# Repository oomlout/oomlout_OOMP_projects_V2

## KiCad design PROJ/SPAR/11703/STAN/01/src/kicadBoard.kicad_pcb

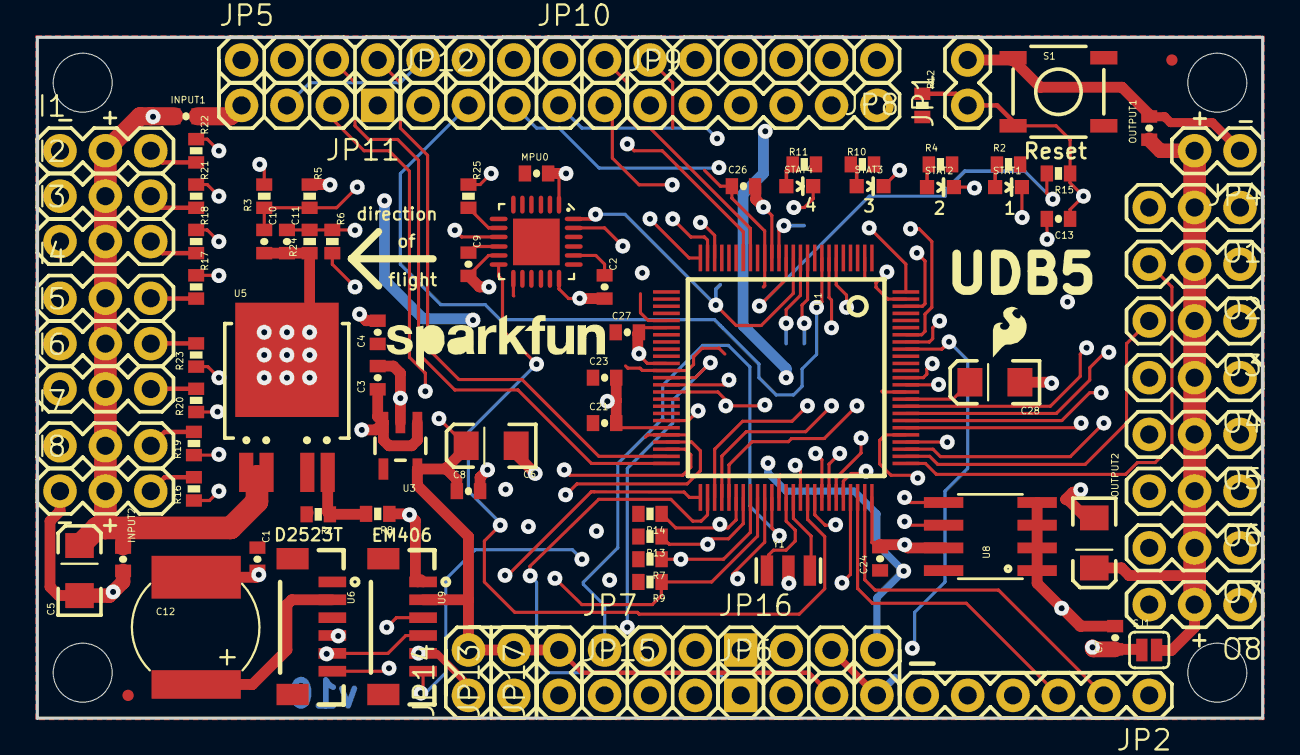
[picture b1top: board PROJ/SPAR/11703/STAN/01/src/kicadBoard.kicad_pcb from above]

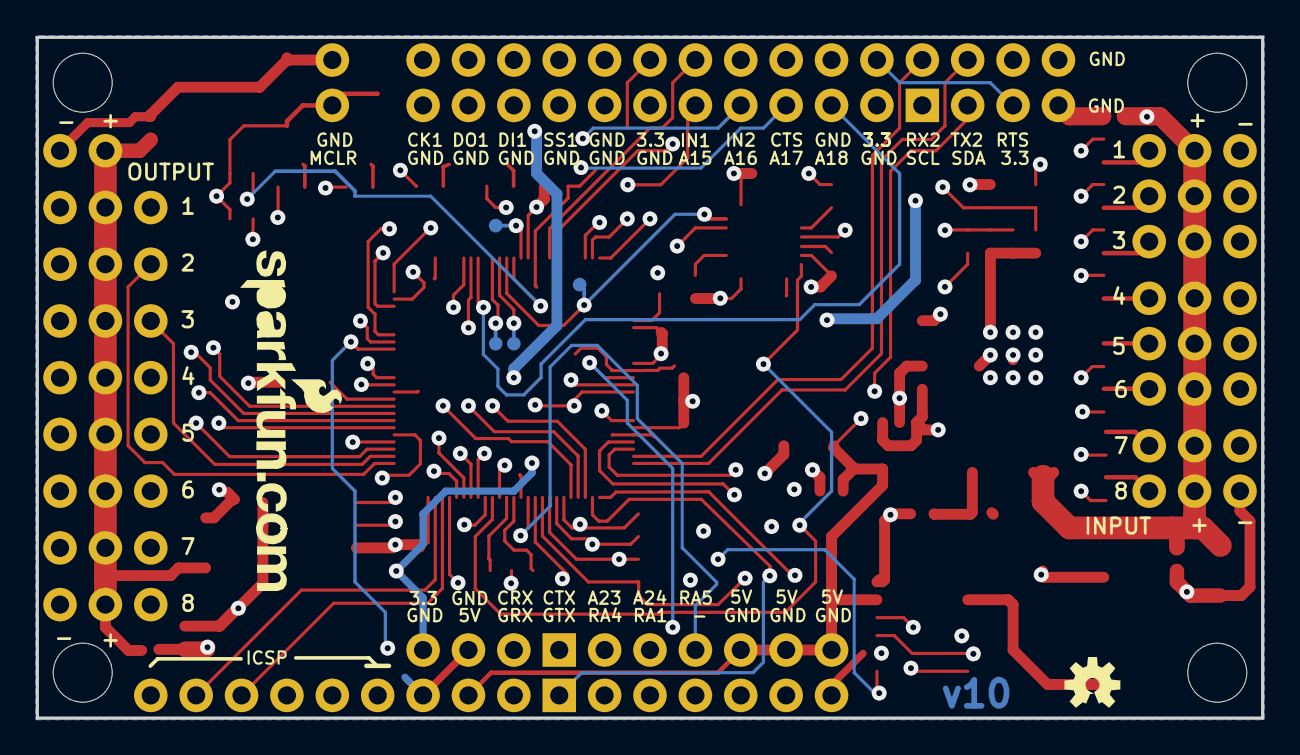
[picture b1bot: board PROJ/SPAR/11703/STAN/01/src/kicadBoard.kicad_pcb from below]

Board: 4 copper layers, 68.6 x 38.1 mm, 110 parts (6 on the bottom side), 84 nets.

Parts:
C1, C3: 1uF; 0402-CAP
C2: 2.2nF; 0402-CAP
C4, C7, C8, C9, C13, C21, C23, C24, C26, C27: 0.1uF; 0402-CAP
C5, C6, C28: 10uF; EIA3216
C10, C11: 22nF; 0402-CAP
C12: 0.2F/3.3V; EN_J2
CC_TEXT1: CREATIVE_COMMONS
I1, I2, I3, I4, I5, I6, I7, I8: S; 1X03
INPUT1, INPUT2: 0.1uF; 0402-CAP
JP1: EXT_Reset; 1X02
JP2: prog; 1X06
JP3: LOGO-SFENEW; SFE-NEW-WEBLOGO
JP4: SVCC; 1X02
JP5: ST; 1X07
JP6: SG; 1X04
JP7, JP15: extra; 1X03
JP8: SPI1; 1X06
JP9: GND; 1X06
JP10: INT; 1X02
JP11: I2C; 1X04
JP12: ACOM1; 1X05
JP13, JP14, JP17: power; 1X02
JP16: extra; 1X04
JP18, JP19: FIDUCIAL1X2.5; FIDUCIAL-1X2.5
LOGO1: LOGO-SFENW2; SFE-NEW-WEB
MPU0: 0.1uF; 0402-CAP
O1, O2, O3, O4, O5, O6, O7, O8: RA; 1X03
OUTPUT1: 0.1uF; 0402-CAP
OUTPUT2: 10uF; EIA3216
R1: 20k; 0402-RES
R2, R4, R10, R11, R16, R17, R18, R19, R20, R21, R22, R23: 330; 0402-RES
R3, R5, R6, R12, R24: 10k; 0402-RES
R7, R9, R13, R14: 4.7k; 0402-RES
R8: 12.1k; 0402-RES
R15: 470; 0402-RES
R25: 1k; 0402-RES
S1: SWITCH-MOMENTARY-2SMD; TACTILE_SWITCH_SMD
SJ1: SOLDERJUMPERNC; SJ_2S
STAT1: red; LED-0603
STAT2: green; LED-0603
STAT3: yellow; LED-0603
STAT4: blue; LED-0603
TP1, TP2, TP3, TP4: TEST-POINT3; PAD.03X.03
U1: DSPIC33FJ256GP710_; TQFP-100-12X12MM
U3: V_REG_LDOSMD; SOT23-5
U5: V_REG_NCP50X; DPAK-5
U6: D2523T_; EM406
U8: EEPROM-I2CSMD; SO08
U9: EM406
U10: MPU-6000QFN-24; QFN-24-TESTING
U$2, U$3, U$4, U$5: STAND-OFF
U$9: OSHW-LOGOS; OSHW-LOGO-S
U$10: LOGO-SFESK; SFE-LOGO-FLAME
Y1: RESONATORSMD; RESONATOR-SMD

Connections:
3.3V: C1.1, C4.1, C21.1, C23.1, C24.1, C26.1, C27.1, JP2.5, JP5.5, JP8.6, JP11.3, JP16.4, MPU0.1, R1.2, R2.2, R4.2, R7.2, R9.2, R10.2, R11.2, R12.2, R13.2, R14.2, U1.2, U1.16, U1.30, U1.37, U1.46, U1.62, U1.86, U5.VOUT, U6.3, U8.8, U10.13
5V: C6.A, C8.1, JP6.3, JP13.2, JP14.2, JP17.2, R6.2, U3.5, U9.2
A-5V: C11.1, R6.1, R24.2, U1.24
A-VCC: C10.1, R3.1, R5.2, U1.25
AN15: JP12.5, U1.44
AN16: JP12.4, U1.6
AN17: JP12.3, U1.7
AN18: JP12.2, U1.8
AN23: JP7.3, U1.92
AN24: JP7.2, U1.93
CRX: JP16.2, U1.87
CTS2: JP5.7, U1.40
CTX: JP16.1, U1.88
GND: C1.2, C2.2, C3.2, C4.2, C5.C, C6.C, C7.2, C8.2, C9.2, C10.2, C11.2, C12.-, C13.2, C21.2, C23.2, C24.2, C26.2, C27.2, C28.C, I1.1, I2.1, I3.1, I4.1, I5.1, I6.1, I7.1, I8.1, INPUT1.2, INPUT2.2, JP1.2, JP2.4, JP4.1, JP5.1, JP5.6, JP6.4, JP8.5, JP9.1, JP9.2, JP9.3, JP9.4, JP9.5, JP9.6, JP11.4, JP12.1, JP13.1, JP14.1, JP16.3, JP17.1, MPU0.2, O1.1, O2.1, O3.1, O4.1, O5.1, O6.1, O7.1, O8.1, OUTPUT1.2, OUTPUT2.C, R5.1, R8.1, R24.1, S1.1, U1.15, U1.31, U1.36, U1.45, U1.65, U1.75, U3.2, U5.GND, U6.4, U8.1, U8.2, U8.3, U8.4, U8.7, U9.1, U9.5, U10.1, U10.11, U10.18, Y1.2
GPS_PPS: U1.67, U9.6
GPS_RX: JP6.2, U1.51, U6.6, U9.3
GPS_TX: JP6.1, U1.52, U6.5, U9.4
I1: R22.1, U1.68
I2: R21.1, U1.69
I3: R18.1, U1.70
I4: R17.1, U1.71
I5: R23.1, U1.79
I6: R20.1, U1.80
I7: R19.1, U1.47
I8: R16.1, U1.48
INT1: JP10.2, U1.18
INT2: JP10.1, U1.19
LED1: STAT1.C, U1.94
LED2: STAT2.C, U1.98
LED3: STAT3.C, U1.99
LED4: STAT4.C, U1.100
MCLR: C13.1, JP1.1, JP2.6, R12.1, R15.1, S1.3
MPU-CS: R25.1, TP1.P$1, U1.14
MPU-INT: U1.66, U10.12
MPU-MISO: TP3.P$1, U1.11, U10.9
MPU-MOSI: TP4.P$1, U1.12, U10.24
MPU-SCK: TP2.P$1, U1.10, U10.23
unnamed: R2.1, STAT1.A
unnamed: R4.1, STAT2.A
unnamed: U1.64, Y1.3
unnamed: C12.+, U6.2
unnamed: R25.2, U10.8
unnamed: U1.63, Y1.1
unnamed: R15.2, U1.13
unnamed: R1.1, R8.2, U5.ADJ
unnamed: C2.1, U10.20
unnamed: I8.3, R16.2
unnamed: I4.3, R17.2
unnamed: C9.1, U10.10
unnamed: I3.3, R18.2
unnamed: I7.3, R19.2
unnamed: I6.3, R20.2
unnamed: I2.3, R21.2
unnamed: I1.3, R22.2
unnamed: I5.3, R23.2
unnamed: R10.1, STAT3.A
unnamed: R11.1, STAT4.A
unnamed: C28.A, U1.85
O1: O1.3, U1.72
O2: O2.3, U1.76
O3: O3.3, U1.77
O4: O4.3, U1.78
O5: O5.3, U1.81
O6: O6.3, U1.82
O7: O7.3, U1.83
O8: O8.3, U1.84
PGEC2: JP2.2, U1.74
PGED2: JP2.3, U1.73
RA1: JP15.2, U1.38
RA4: JP15.3, U1.60
RA5: JP7.1, U1.61
RTS2: JP5.2, U1.39
RX2: JP5.4, U1.49
SCK1: JP8.1, U1.55
SCL1: R13.1, U1.57, U8.6
SCL2: JP11.1, R7.1, U1.58
SDA1: R14.1, U1.56, U8.5
SDA2: JP11.2, R9.1, U1.59
SDI1: JP8.3, U1.54
SDO1: JP8.2, U1.53
SS1: JP8.4, U1.23
SVCC: JP4.2, O1.2, O2.2, O3.2, O4.2, O5.2, O6.2, O7.2, O8.2, OUTPUT1.1, OUTPUT2.A, SJ1.2
TX2: JP5.3, U1.50
VCC: C3.1, C5.A, C7.1, I1.2, I2.2, I3.2, I4.2, I5.2, I6.2, I7.2, I8.2, INPUT1.1, INPUT2.1, R3.2, SJ1.1, U3.1, U3.3, U5.EN, U5.VIN

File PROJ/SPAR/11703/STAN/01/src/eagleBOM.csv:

"Part";"Value";"Device";"Package";"Description";"";
"C1";"1uF";"CAP0402-CAP";"0402-CAP";"Capacitor";"";
"C2";"2.2nF";"CAP0402-CAP";"0402-CAP";"Capacitor";"";
"C3";"1uF";"CAP0402-CAP";"0402-CAP";"Capacitor";"";
"C4";"0.1uF";"CAP0402-CAP";"0402-CAP";"Capacitor";"";
"C5";"10uF";"CAP_POL1206";"EIA3216";"Capacitor Polarized";"";
"C6";"10uF";"CAP_POL1206";"EIA3216";"Capacitor Polarized";"";
"C7";"0.1uF";"CAP0402-CAP";"0402-CAP";"Capacitor";"";
"C8";"0.1uF";"CAP0402-CAP";"0402-CAP";"Capacitor";"";
"C9";"0.1uF";"CAP0402-CAP";"0402-CAP";"Capacitor";"";
"C10";"22nF";"CAP0402-CAP";"0402-CAP";"Capacitor";"";
"C11";"22nF";"CAP0402-CAP";"0402-CAP";"Capacitor";"";
"C12";"0.2F/3.3V";"CAP_POLEN_J2";"EN_J2";"Capacitor Polarized";"";
"C13";"0.1uF";"CAP0402-CAP";"0402-CAP";"Capacitor";"";
"C21";"0.1uF";"CAP0402-CAP";"0402-CAP";"Capacitor";"";
"C23";"0.1uF";"CAP0402-CAP";"0402-CAP";"Capacitor";"";
"C24";"0.1uF";"CAP0402-CAP";"0402-CAP";"Capacitor";"";
"C26";"0.1uF";"CAP0402-CAP";"0402-CAP";"Capacitor";"";
"C27";"0.1uF";"CAP0402-CAP";"0402-CAP";"Capacitor";"";
"C28";"10uF";"CAP_POL1206";"EIA3216";"Capacitor Polarized";"";
"CC_TEXT1";"CREATIVE_COMMONS";"CREATIVE_COMMONS";"CREATIVE_COMMONS";"Creative Commons License summary";"";
"I1";"S";"M03PTH";"1X03";"Header 3";"";
"I2";"S";"M03PTH";"1X03";"Header 3";"";
"I3";"S";"M03PTH";"1X03";"Header 3";"";
"I4";"S";"M03PTH";"1X03";"Header 3";"";
"I5";"S";"M03PTH";"1X03";"Header 3";"";
"I6";"S";"M03PTH";"1X03";"Header 3";"";
"I7";"S";"M03PTH";"1X03";"Header 3";"";
"I8";"S";"M03PTH";"1X03";"Header 3";"";
"INPUT1";"0.1uF";"CAP0402-CAP";"0402-CAP";"Capacitor";"";
"INPUT2";"0.1uF";"CAP0402-CAP";"0402-CAP";"Capacitor";"";
"JP1";"EXT_Reset";"M02PTH";"1X02";"Header 2";"";
"JP2";"prog";"M06SIP";"1X06";"Header 6";"";
"JP3";"LOGO-SFENEW";"LOGO-SFENEW";"SFE-NEW-WEBLOGO";"Spark Fun Electronics PCB Logo";"";
"JP4";"SVCC";"M02PTH";"1X02";"Header 2";"";
"JP5";"ST";"M07";"1X07";"Header 7";"";
"JP6";"SG";"M04PTH";"1X04";"Header 4";"";
"JP7";"extra";"M03PTH";"1X03";"Header 3";"";
"JP8";"SPI1";"M06SIP";"1X06";"Header 6";"";
"JP9";"GND";"M06SIP";"1X06";"Header 6";"";
"JP10";"INT";"M02PTH";"1X02";"Header 2";"";
"JP11";"I2C";"M04PTH";"1X04";"Header 4";"";
"JP12";"ACOM1";"M05PTH";"1X05";"Header 5";"";
"JP13";"power";"M02PTH";"1X02";"Header 2";"";
"JP14";"power";"M02PTH";"1X02";"Header 2";"";
"JP15";"extra";"M03PTH";"1X03";"Header 3";"";
"JP16";"extra";"M04PTH";"1X04";"Header 4";"";
"JP17";"power";"M02PTH";"1X02";"Header 2";"";
"JP18";"FIDUCIAL1X2.5";"FIDUCIAL1X2.5";"FIDUCIAL-1X2.5";"Fiducial Alignment Points";"";
"JP19";"FIDUCIAL1X2.5";"FIDUCIAL1X2.5";"FIDUCIAL-1X2.5";"Fiducial Alignment Points";"";
"LOGO1";"LOGO-SFENW2";"LOGO-SFENW2";"SFE-NEW-WEB";"Spark Fun Electronics PCB Logo";"";
"MPU";"0.1uF";"CAP0402-CAP";"0402-CAP";"Capacitor";"";
"O1";"RA";"M03PTH";"1X03";"Header 3";"";
"O2";"RA";"M03PTH";"1X03";"Header 3";"";
"O3";"RA";"M03PTH";"1X03";"Header 3";"";
"O4";"RA";"M03PTH";"1X03";"Header 3";"";
"O5";"RA";"M03PTH";"1X03";"Header 3";"";
"O6";"RA";"M03PTH";"1X03";"Header 3";"";
"O7";"RA";"M03PTH";"1X03";"Header 3";"";
"O8";"RA";"M03PTH";"1X03";"Header 3";"";
"OUTPUT1";"0.1uF";"CAP0402-CAP";"0402-CAP";"Capacitor";"";
"OUTPUT2";"10uF";"CAP_POL1206";"EIA3216";"Capacitor Polarized";"";
"R1";"20k";"RESISTOR0402-RES";"0402-RES";"Resistor";"";
"R2";"330";"RESISTOR0402-RES";"0402-RES";"Resistor";"";
"R3";"10k";"RESISTOR0402-RES";"0402-RES";"Resistor";"";
"R4";"330";"RESISTOR0402-RES";"0402-RES";"Resistor";"";
"R5";"10k";"RESISTOR0402-RES";"0402-RES";"Resistor";"";
"R6";"10k";"RESISTOR0402-RES";"0402-RES";"Resistor";"";
"R7";"4.7k";"RESISTOR0402-RES";"0402-RES";"Resistor";"";
"R8";"12.1k";"RESISTOR0402-RES";"0402-RES";"Resistor";"";
"R9";"4.7k";"RESISTOR0402-RES";"0402-RES";"Resistor";"";
"R10";"330";"RESISTOR0402-RES";"0402-RES";"Resistor";"";
"R11";"330";"RESISTOR0402-RES";"0402-RES";"Resistor";"";
"R12";"10k";"RESISTOR0402-RES";"0402-RES";"Resistor";"";
"R13";"4.7k";"RESISTOR0402-RES";"0402-RES";"Resistor";"";
"R14";"4.7k";"RESISTOR0402-RES";"0402-RES";"Resistor";"";
"R15";"470";"RESISTOR0402-RES";"0402-RES";"Resistor";"";
"R16";"330";"RESISTOR0402-RES";"0402-RES";"Resistor";"";
"R17";"330";"RESISTOR0402-RES";"0402-RES";"Resistor";"";
"R18";"330";"RESISTOR0402-RES";"0402-RES";"Resistor";"";
"R19";"330";"RESISTOR0402-RES";"0402-RES";"Resistor";"";
"R20";"330";"RESISTOR0402-RES";"0402-RES";"Resistor";"";
"R21";"330";"RESISTOR0402-RES";"0402-RES";"Resistor";"";
"R22";"330";"RESISTOR0402-RES";"0402-RES";"Resistor";"";
"R23";"330";"RESISTOR0402-RES";"0402-RES";"Resistor";"";
"R24";"10k";"RESISTOR0402-RES";"0402-RES";"Resistor";"";
"R25";"1k";"RESISTOR0402-RES";"0402-RES";"Resistor";"";
"S1";"SWITCH-MOMENTARY-2SMD";"SWITCH-MOMENTARY-2SMD";"TACTILE_SWITCH_SMD";"";"";
"SJ1";"SOLDERJUMPERNC";"SOLDERJUMPERNC";"SJ_2S";"Solder Jumper";"";
"STAT1";"red";"LED0603";"LED-0603";"LEDs";"";
"STAT2";"green";"LED0603";"LED-0603";"LEDs";"";
"STAT3";"yellow";"LED0603";"LED-0603";"LEDs";"";
"STAT4";"blue";"LED0603";"LED-0603";"LEDs";"";
"TP1";"TEST-POINT3";"TEST-POINT3";"PAD.03X.03";"Bare copper test points for troubleshooting or ICT";"";
"TP2";"TEST-POINT3";"TEST-POINT3";"PAD.03X.03";"Bare copper test points for troubleshooting or ICT";"";
"TP3";"TEST-POINT3";"TEST-POINT3";"PAD.03X.03";"Bare copper test points for troubleshooting or ICT";"";
"TP4";"TEST-POINT3";"TEST-POINT3";"PAD.03X.03";"Bare copper test points for troubleshooting or ICT";"";
"U$2";"STAND-OFF";"STAND-OFF";"STAND-OFF";"Stand Off";"";
"U$3";"STAND-OFF";"STAND-OFF";"STAND-OFF";"Stand Off";"";
"U$4";"STAND-OFF";"STAND-OFF";"STAND-OFF";"Stand Off";"";
"U$5";"STAND-OFF";"STAND-OFF";"STAND-OFF";"Stand Off";"";
"U$9";"OSHW-LOGOS";"OSHW-LOGOS";"OSHW-LOGO-S";"Open Source Hardware Logo This logo indicates the piece of hardware it is found on incorporates a OSHW license and/or adheres to the definition of open source hardware found here: http://freedomdefined.org/OSHW";"";
"U$10";"LOGO-SFESK";"LOGO-SFESK";"SFE-LOGO-FLAME";"Spark Fun Electronics PCB Logo";"";
"U1";"DSPIC33FJ256GP710_";"DSPIC33FJ256GP710_";"TQFP-100-12X12MM";"";"";
"U3";"V_REG_LDOSMD";"V_REG_LDOSMD";"SOT23-5";"Voltage Regulator LDO";"";
"U5";"V_REG_NCP50X";"V_REG_NCP50X";"DPAK-5";"NCP550x 500mA LDO Voltage Regulator";"";
"U6";"D2523T_";"D2523T_";"EM406";"D2523T GPS Module";"";
"U8";"EEPROM-I2CSMD";"EEPROM-I2CSMD";"SO08";"";"";
"U9";"EM406";"EM406";"EM406";"EM406 Connector";"";
"U10";"MPU-6000QFN-24";"MPU-6000QFN-24";"QFN-24-TESTING";"MPU-6000 - I2C address is 0x68 with AD0 low and 0x69 with AD0 high.";"";
"Y1";"RESONATORSMD";"RESONATORSMD";"RESONATOR-SMD";"Resonator";"";

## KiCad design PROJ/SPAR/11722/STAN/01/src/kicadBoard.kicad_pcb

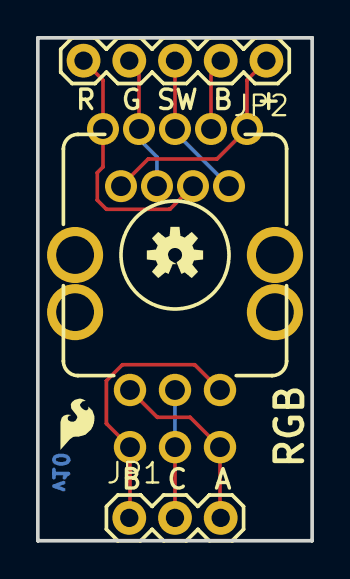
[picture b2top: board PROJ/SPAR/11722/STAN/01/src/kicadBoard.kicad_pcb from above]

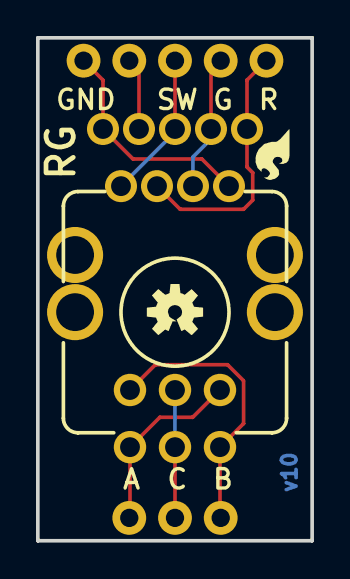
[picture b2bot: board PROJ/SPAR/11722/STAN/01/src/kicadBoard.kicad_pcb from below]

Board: 2 copper layers, 15.2 x 27.9 mm, 9 parts (3 on the bottom side), 8 nets.

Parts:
FRAME1: FRAME-LETTER; CREATIVE_COMMONS
JP1: 1X03
JP2: 1X05
JP3, JP4: LOGO-SFESK; SFE-LOGO-FLAME
SW1: ENCODER_LED_3_KIT
U1: ENCODER_2LEDKIT; ENCODER_LED_2_KIT
U$1, U$2: OSHW-LOGOS; OSHW-LOGO-S

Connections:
A: JP1.3, SW1.A, U1.A
B: JP1.1, SW1.B, U1.B
BLUE: JP2.2, SW1.4
C: JP1.2, SW1.C, U1.C
COMMON: JP2.1, SW1.5, U1.GND
GREEN: JP2.4, SW1.2, U1.+G
RED: JP2.5, SW1.1, U1.+R
SWITCH: JP2.3, SW1.3, U1.SW

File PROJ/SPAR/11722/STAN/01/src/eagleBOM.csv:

"Part";"Value";"Device";"Package";"Description";"";
"FRAME1";"FRAME-LETTER";"FRAME-LETTER";"CREATIVE_COMMONS";"Schematic Frame";"";
"JP1";"";"M03PTH";"1X03";"Header 3";"";
"JP2";"";"M05PTH";"1X05";"Header 5";"";
"JP3";"LOGO-SFESK";"LOGO-SFESK";"SFE-LOGO-FLAME";"Spark Fun Electronics PCB Logo";"";
"JP4";"LOGO-SFESK";"LOGO-SFESK";"SFE-LOGO-FLAME";"Spark Fun Electronics PCB Logo";"";
"SW1";"";"ENCODER_RGB_CAKIT";"ENCODER_LED_3_KIT";"Illuminated Rotary Encoder w/ RGB LED and select switch";"";
"U$2";"OSHW-LOGOS";"OSHW-LOGOS";"OSHW-LOGO-S";"Open Source Hardware Logo This logo indicates the piece of hardware it is found on incorporates a OSHW license and/or adheres to the definition of open source hardware found here: http://freedomdefined.org/OSHW";"";
"U1";"ENCODER_2LEDKIT";"ENCODER_2LEDKIT";"ENCODER_LED_2_KIT";"Illuminated Rotary Encoder w/ 2 LEDs";"";

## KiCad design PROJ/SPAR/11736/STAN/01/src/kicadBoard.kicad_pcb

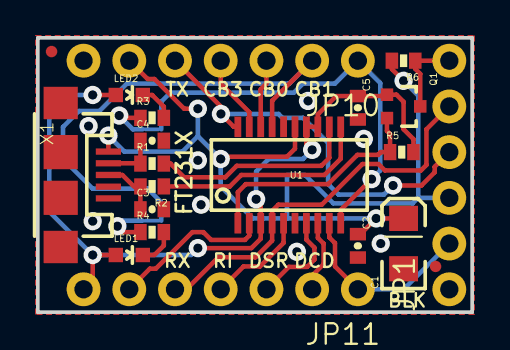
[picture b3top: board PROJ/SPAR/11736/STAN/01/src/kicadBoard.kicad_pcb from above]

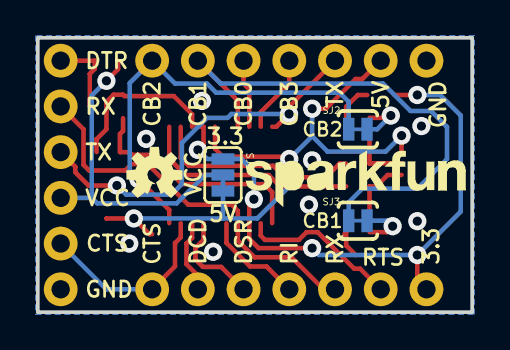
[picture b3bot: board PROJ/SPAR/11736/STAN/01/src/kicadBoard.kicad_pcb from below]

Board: 2 copper layers, 24.1 x 15.2 mm, 27 parts (5 on the bottom side), 25 nets.

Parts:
C1: 10uF; EIA3216
C2, C5: 0.1uF; 0402-CAP
C3, C4: 47pF; 0402-CAP
FRAME1: FRAME-LETTER; CREATIVE_COMMONS
JP1: 1X06_NS
JP2: LOGO-SFENW2; SFE-NEW-WEB
JP3, JP4: FIDUCIALUFIDUCIAL; MICRO-FIDUCIAL
JP10, JP11: 1X07_NS
LED1: RED; LED-0603
LED2: YELLOW; LED-0603
Q1: 2N7002PW; SOT323
R1, R2: 27; 0402-RES
R3, R4: 1k; 0402-RES
R5, R6: 10k; 0402-RES
SJ1: SJ_3
SJ2: TXLED; SJ_2S-TRACE
SJ3: RXLED; SJ_2S-TRACE
U1: FT231XS; SSOP20_L
U$1: OSHW-LOGOS; OSHW-LOGO-S
X1: USB-MICROB

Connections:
3.3V: C5.1, JP11.7, LED1.A, LED2.A, Q1.1, R5.2, SJ1.1, U1.3, U1.13, U1.14
CBUS0: JP10.3, U1.18
CBUS3: JP10.4, U1.19
CTS: JP1.2, JP11.1, U1.9
DCD: JP11.2, U1.8
DSR: JP11.3, U1.7
DTR: Q1.2, R5.1, U1.1
GND: C1.C, C2.2, C3.2, C4.2, C5.2, JP1.1, JP10.7, U1.6, U1.16, X1.GND, X1.MT1, X1.MT2
unnamed: R1.2, U1.12
unnamed: R2.1, U1.11
unnamed: C3.1, R2.2, X1.D+
unnamed: C4.1, R1.1, X1.D-
unnamed: LED2.C, R3.2
unnamed: LED1.C, R4.2
unnamed: R3.1, SJ2.2
unnamed: R4.1, SJ3.2
RESET: JP1.6, Q1.3, R6.1
RI: JP11.4, U1.5
RTS: JP11.6, U1.2
RXD: JP1.5, JP11.5, U1.4
RXLED: JP10.2, SJ3.1, U1.17
TXD: JP1.4, JP10.5, U1.20
TXLED: JP10.1, SJ2.1, U1.10
VCC: C1.A, C2.1, JP10.6, SJ1.3, U1.15, X1.VBUS
VOUT: JP1.3, R6.2, SJ1.2

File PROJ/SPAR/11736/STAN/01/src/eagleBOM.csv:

"Part";"Value";"Device";"Package";"Description";"PROD_ID";
"C1";"10uF";"CAP_POL1206";"EIA3216";"Capacitor Polarized";"";
"C2";"0.1uF";"CAP0402-CAP";"0402-CAP";"Capacitor";"";
"C3";"47pF";"CAP0402-CAP";"0402-CAP";"Capacitor";"";
"C4";"47pF";"CAP0402-CAP";"0402-CAP";"Capacitor";"";
"C5";"0.1uF";"CAP0402-CAP";"0402-CAP";"Capacitor";"";
"FRAME1";"FRAME-LETTER";"FRAME-LETTER";"CREATIVE_COMMONS";"Schematic Frame";"";
"JP1";"";"M06SIP-NS";"1X06_NS";"Header 6";"";
"JP2";"LOGO-SFENW2";"LOGO-SFENW2";"SFE-NEW-WEB";"Spark Fun Electronics PCB Logo";"";
"JP3";"FIDUCIALUFIDUCIAL";"FIDUCIALUFIDUCIAL";"MICRO-FIDUCIAL";"Fiducial Alignment Points";"";
"JP4";"FIDUCIALUFIDUCIAL";"FIDUCIALUFIDUCIAL";"MICRO-FIDUCIAL";"Fiducial Alignment Points";"";
"JP10";"";"M07NS";"1X07_NS";"Header 7";"";
"JP11";"";"M07NS";"1X07_NS";"Header 7";"";
"LED1";"RED";"LED0603";"LED-0603";"LEDs";"";
"LED2";"YELLOW";"LED0603";"LED-0603";"LEDs";"";
"Q1";"2N7002PW";"MOSFET-NCHANNELSOT323";"SOT323";"Generic NMOS footprint";"";
"R1";"27";"RESISTOR0402-RES";"0402-RES";"Resistor";"";
"R2";"27";"RESISTOR0402-RES";"0402-RES";"Resistor";"";
"R3";"1k";"RESISTOR0402-RES";"0402-RES";"Resistor";"";
"R4";"1k";"RESISTOR0402-RES";"0402-RES";"Resistor";"";
"R5";"10k";"RESISTOR0402-RES";"0402-RES";"Resistor";"";
"R6";"10k";"RESISTOR0402-RES";"0402-RES";"Resistor";"";
"SJ1";"";"SOLDERJUMPER_2WAYS";"SJ_3";"Solder Jumper";"";
"SJ2";"TXLED";"SOLDERJUMPERTRACE";"SJ_2S-TRACE";"Solder Jumper";"";
"SJ3";"RXLED";"SOLDERJUMPERTRACE";"SJ_2S-TRACE";"Solder Jumper";"";
"U$1";"OSHW-LOGOS";"OSHW-LOGOS";"OSHW-LOGO-S";"Open Source Hardware Logo This logo indicates the piece of hardware it is found on incorporates a OSHW license and/or adheres to the definition of open source hardware found here: http://freedomdefined.org/OSHW";"";
"U1";"FT231XS";"FT231XS";"SSOP20_L";"FTDI FT231X Full Speed USB to Full-handshake UART";"";
"X1";"USB-MICROB";"USB-MICROB";"USB-MICROB";"USB Connectors";"CONN-09505";

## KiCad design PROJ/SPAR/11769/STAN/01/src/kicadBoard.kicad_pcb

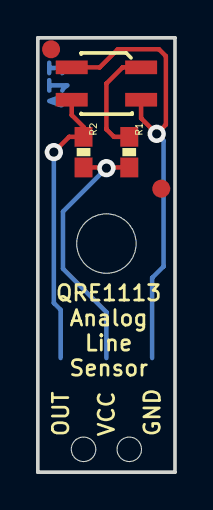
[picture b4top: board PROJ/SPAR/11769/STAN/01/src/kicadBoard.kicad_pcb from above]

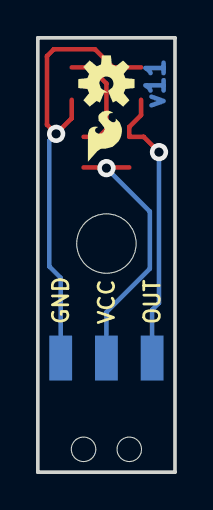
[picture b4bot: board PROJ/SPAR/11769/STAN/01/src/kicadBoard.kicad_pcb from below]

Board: 4 copper layers, 7.6 x 24.1 mm, 10 parts (3 on the bottom side), 4 nets.

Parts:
FID1, FID2: FIDUCIAL1X2; FIDUCIAL-1X2
FRAME1: FRAME-LETTER; CREATIVE_COMMONS
JP1: 1X03_SMD_RA_MALE_POST_SMALLER
LOGO2: OSHW-LOGOS; OSHW-LOGO-S
LOGO3: LOGO-SFESK; SFE-LOGO-FLAME
R1: 100; 0603-RES
R2: 10k; 0603-RES
STANDOFF1: STAND-OFF
U1: QRE1113SMD-W; QRE1113-W

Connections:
5V: JP1.2, R1.2, R2.2
GND: JP1.1, U1.2, U1.4
unnamed: R1.1, U1.1
unnamed: JP1.3, R2.1, U1.3

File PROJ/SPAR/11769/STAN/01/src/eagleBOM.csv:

"Part";"Value";"Device";"Package";"Description";"PROD_ID";"VALUE";
"FID1";"FIDUCIAL1X2";"FIDUCIAL1X2";"FIDUCIAL-1X2";"Fiducial Alignment Points";"";"";
"FID2";"FIDUCIAL1X2";"FIDUCIAL1X2";"FIDUCIAL-1X2";"Fiducial Alignment Points";"";"";
"FRAME1";"FRAME-LETTER";"FRAME-LETTER";"CREATIVE_COMMONS";"Schematic Frame";"";"";
"JP1";"";"M031X03_SMD_RA_MALE_POST_SMALLER";"1X03_SMD_RA_MALE_POST_SMALLER";"Header 3";"";"";
"LOGO2";"OSHW-LOGOS";"OSHW-LOGOS";"OSHW-LOGO-S";"Open Source Hardware Logo This logo indicates the piece of hardware it is found on incorporates a OSHW license and/or adheres to the definition of open source hardware found here: http://freedomdefined.org/OSHW";"";"";
"LOGO3";"LOGO-SFESK";"LOGO-SFESK";"SFE-LOGO-FLAME";"Spark Fun Electronics PCB Logo";"";"";
"R1";"100";"100-1%";"0603-RES";"100-ohm SMT";"RES-07863";"100";
"R2";"10k";"10KOHM1/10W1%(0603)0603";"0603-RES";"RES-00824";"RES-00824";"10K";
"STANDOFF1";"STAND-OFF";"STAND-OFF";"STAND-OFF";"#4 Stand Off";"";"";
"U1";"QRE1113SMD-W";"QRE1113SMD-W";"QRE1113-W";"Reflective object sensor";"";"";

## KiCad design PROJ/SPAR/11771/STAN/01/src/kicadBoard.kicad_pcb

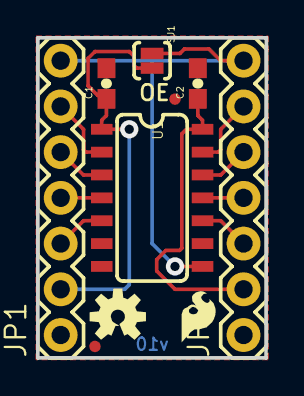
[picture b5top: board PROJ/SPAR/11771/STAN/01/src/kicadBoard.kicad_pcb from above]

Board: 4 copper layers, 12.7 x 17.8 mm, 11 parts (0 on the bottom side), 12 nets.

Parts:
C1, C2: 0.1uF; 0603-CAP
FID1, FID2: FIDUCIALUFIDUCIAL; MICRO-FIDUCIAL
FRAME1: FRAME-LETTER; CREATIVE_COMMONS
JP1, JP2: 1X07
LOGO1: LOGO-SFESK; SFE-LOGO-FLAME
LOGO2: OSHW-LOGOS; OSHW-LOGO-S
SJ1: SOLDERJUMPERNC2; SJ_2S-NOTRACE
U1: SO14

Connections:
3.3V: C1.1, JP1.2, SJ1.2, U1.1
5V: C2.1, JP2.2, U1.14
B1: JP2.6, U1.13
B2: JP2.5, U1.12
B3: JP2.4, U1.11
B4: JP2.3, U1.10
GND: C1.2, C2.2, JP1.1, JP2.1, U1.7
unnamed: JP1.3, U1.5
unnamed: JP1.4, U1.4
unnamed: JP1.5, U1.3
unnamed: JP1.6, U1.2
OE: JP1.7, JP2.7, SJ1.1, U1.8

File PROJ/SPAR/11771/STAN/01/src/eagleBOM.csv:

"Part";"Value";"Device";"Package";"Description";"PROD_ID";"VALUE";
"C1";"0.1uF";"0.1UF-25V(+80/-20%)(0603)";"0603-CAP";"Ceramic";"CAP-00810";"0.1uF";
"C2";"0.1uF";"0.1UF-25V(+80/-20%)(0603)";"0603-CAP";"Ceramic";"CAP-00810";"0.1uF";
"FID1";"FIDUCIALUFIDUCIAL";"FIDUCIALUFIDUCIAL";"MICRO-FIDUCIAL";"Fiducial Alignment Points";"";"";
"FID2";"FIDUCIALUFIDUCIAL";"FIDUCIALUFIDUCIAL";"MICRO-FIDUCIAL";"Fiducial Alignment Points";"";"";
"FRAME1";"FRAME-LETTER";"FRAME-LETTER";"CREATIVE_COMMONS";"Schematic Frame";"";"";
"JP1";"";"M07";"1X07";"Header 7";"";"";
"JP2";"";"M07";"1X07";"Header 7";"";"";
"LOGO1";"LOGO-SFESK";"LOGO-SFESK";"SFE-LOGO-FLAME";"Spark Fun Electronics PCB Logo";"";"";
"LOGO2";"OSHW-LOGOS";"OSHW-LOGOS";"OSHW-LOGO-S";"Open Source Hardware Logo This logo indicates the piece of hardware it is found on incorporates a OSHW license and/or adheres to the definition of open source hardware found here: http://freedomdefined.org/OSHW";"";"";
"SJ1";"SOLDERJUMPERNC2";"SOLDERJUMPERNC2";"SJ_2S-NOTRACE";"Solder Jumper";"";"";
"U1";"";"TXB0104PWRSOIC14";"SO14";"4-Bit Bi-Directional Level Shifter";"IC-11329";"";

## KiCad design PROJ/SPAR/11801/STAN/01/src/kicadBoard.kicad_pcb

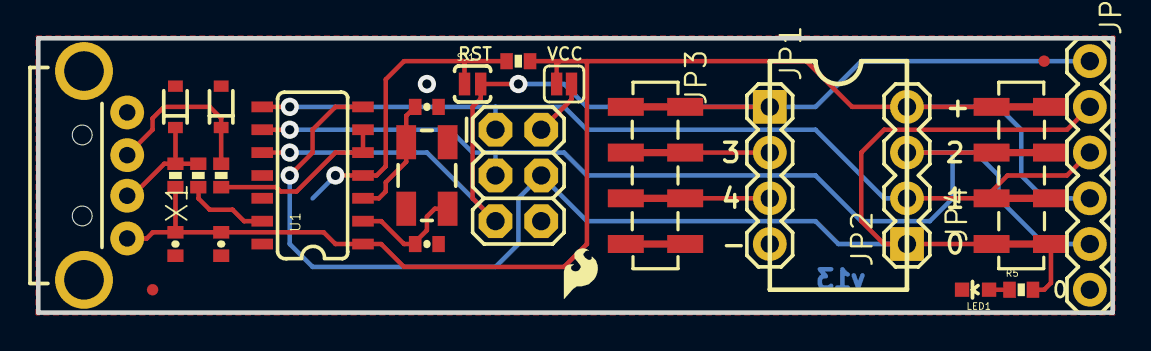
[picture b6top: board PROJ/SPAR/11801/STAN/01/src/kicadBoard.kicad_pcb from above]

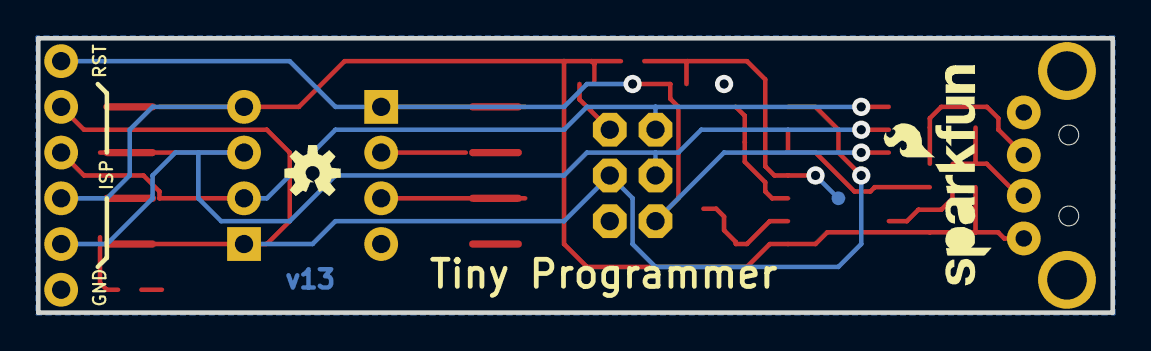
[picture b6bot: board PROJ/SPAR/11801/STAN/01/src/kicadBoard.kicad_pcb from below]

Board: 2 copper layers, 59.7 x 15.2 mm, 31 parts (4 on the bottom side), 17 nets.

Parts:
C1: 0.1uF; 0402-CAP
C2, C4: 18pF; 0402-CAP
C3: 10uF; 0402-CAP
D1, D2: 3.3V; SOD-323
FRAME1: FRAME-LETTER; CREATIVE_COMMONS
JP1, JP2: 1X04
JP3, JP4: 1X04_SMD_STRAIGHT_COMBO
JP5: LOGO-SFENW2; SFE-NEW-WEB
JP6, JP11: LOGO-SFESK; SFE-LOGO-FLAME
JP7, JP8: FIDUCIALUFIDUCIAL; MICRO-FIDUCIAL
JP9: 2X3
JP12: 1X06
LED1: Yellow; LED-0603
Q1: 16MHz; CRYSTAL-SMD-5X3
R1, R2: 68; 0402-RES
R3: 1.5K; 0402-RES
R4: 10k; 0402-RES
R5: 330; 0402-RES
SJ1: SOLDERJUMPERNO; SJ_2S-NO
SJ2: NC; SJ_2S
TP1: TEST-POINT3; PAD.03X.03
U1: ATTINY84; SO14
U$1: OSHW-LOGOS; OSHW-LOGO-S
X1: USB-A-H

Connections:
2: JP1.2, JP3.2
3: JP1.3, JP3.3
D+: R2.2, U1.5, U1.6
D-: R1.2, U1.13
GND: C1.2, C2.2, C3.2, C4.2, D1.2, D2.2, JP1.4, JP3.4, JP9.6, JP12.6, LED1.C, U1.14, X1.GND
MISO: JP2.2, JP4.2, JP9.1, JP12.3, U1.8
MOSI: JP2.1, JP4.1, JP9.4, JP12.2, R5.2, U1.7
unnamed: D2.1, R1.1, R3.1, X1.D-
unnamed: D1.1, R2.1, X1.D+
unnamed: C2.1, Q1.3, U1.3
unnamed: C4.1, Q1.1, U1.2
unnamed: LED1.A, R5.1
RESET: R4.1, SJ1.1, TP1.P$1, U1.4
RST: JP1.1, JP3.1, JP9.5, JP12.1, SJ1.2, U1.10
SCK: JP2.3, JP4.3, JP9.3, JP12.5, U1.9
VCC: C1.1, C3.1, JP2.4, JP4.4, JP12.4, R3.2, R4.2, SJ2.1, U1.1, X1.VBUS
VCC': JP9.2, SJ2.2

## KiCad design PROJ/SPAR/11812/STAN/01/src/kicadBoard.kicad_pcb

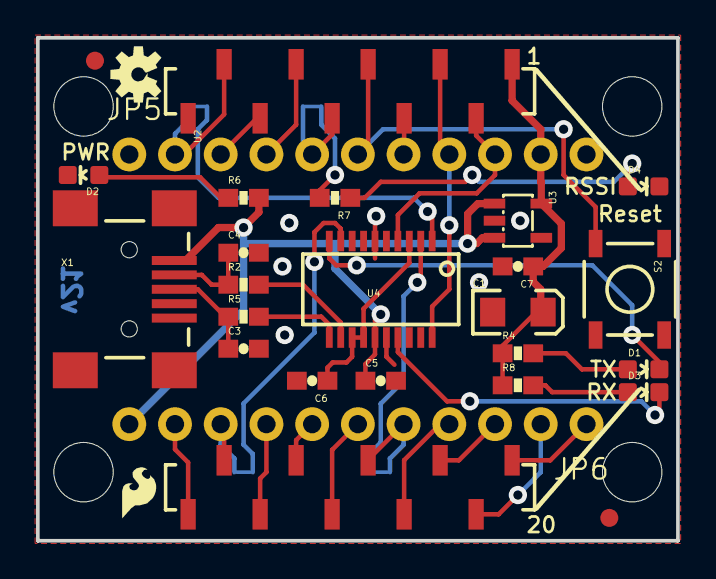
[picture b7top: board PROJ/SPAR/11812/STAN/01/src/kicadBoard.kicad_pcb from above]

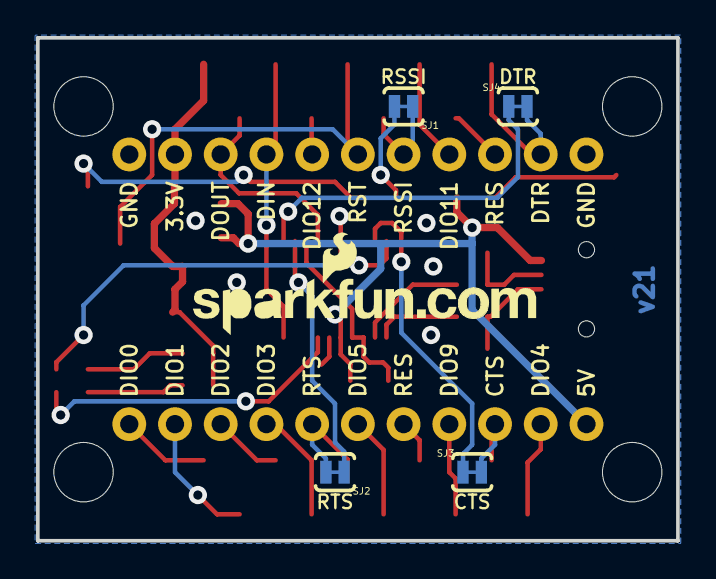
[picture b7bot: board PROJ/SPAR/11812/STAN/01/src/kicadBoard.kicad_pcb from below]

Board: 2 copper layers, 35.6 x 27.9 mm, 37 parts (5 on the bottom side), 36 nets.

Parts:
C1: 10uF; EIA3216
C3, C4: 47pF; 0603-CAP
C5, C6, C7: 0.1uF; 0603-CAP
D1, D2: RED; LED-0603
D3, D4: GREEN; LED-0603
FRAME1: FRAME-LETTER; CREATIVE_COMMONS
JP1, JP4: FIDUCIAL1X2; FIDUCIAL-1X2
JP5, JP6: M111X11_NO_SILK; 1X11_NO_SILK
LOGO1: OSHW-LOGOS; OSHW-LOGO-S
R2, R5: 27; 0603-RES
R4, R6, R8: 1k; 0603-RES
R7: 330; 0603-RES
S2: Reset; TACTILE_SWITCH_SMD
SJ1: RSSI_LED_EN; SJ_2S-TRACE
SJ2: CTS_EN; SJ_2S-TRACE
SJ3: RTS_EN; SJ_2S-TRACE
SJ4: DTR; SJ_2S-TRACE
U2: XBEE-1B3; XBEE-SMD
U3: MIC5219 3.3V; SOT23-5
U4: FT231XS; SSOP20_L
U$1: LOGO-SFESK; SFE-LOGO-FLAME
U$4: LOGO-SFENEW; SFE-NEW-WEBLOGO
U$5, U$9, U$10, U$11: STAND-OFF
X1: USBSMD; USB-MINIB

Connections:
3.3V: C1.A, C7.1, JP5.10, R4.1, R8.1, U2.1, U3.5
3V-INT: C6.1, U4.3, U4.13, U4.14
5V: C5.1, JP6.11, R6.2, U3.1, U3.3, U4.15, X1.VBUS
CTS: SJ3.1, U4.9
CTS_XBEE: JP6.9, SJ3.2, U2.12
DIN: JP5.8, U2.3, U4.20
DIO0: JP6.1, U2.20
DIO1: JP6.2, U2.19
DIO2: JP6.3, U2.18
DIO3: JP6.4, U2.17
DIO4: JP6.10, U2.11
DIO5: JP6.6, U2.15
DIO9: JP6.8, U2.13
DIO11: JP5.4, U2.7
DIO12: JP5.7, U2.4
DOUT: JP5.9, U2.2, U4.4
DTR: SJ4.1, U4.1
DTR_XBEE: JP5.2, SJ4.2, U2.9
GND: C1.C, C3.2, C4.2, C5.2, C6.2, C7.2, D2.C, D4.C, JP5.1, JP5.11, S2.1, U2.10, U3.2, U4.6, U4.16, X1.GND
unnamed: D1.A, R4.2
unnamed: D4.A, R7.1
unnamed: C3.1, R5.1, X1.D+
unnamed: D3.A, R8.2
unnamed: C4.1, R2.1, X1.D-
unnamed: D3.C, U4.17
unnamed: R5.2, U4.11
unnamed: R2.2, U4.12
unnamed: R7.2, SJ1.2
unnamed: D2.A, R6.1
RES1: JP5.3, U2.8
RES2: JP6.7, U2.14
RESET: JP5.6, S2.3, U2.5
RSSI: JP5.5, SJ1.1, U2.6
RTS: SJ2.1, U4.2
RTS_XBEE: JP6.5, SJ2.2, U2.16
TXLED: D1.C, U4.10

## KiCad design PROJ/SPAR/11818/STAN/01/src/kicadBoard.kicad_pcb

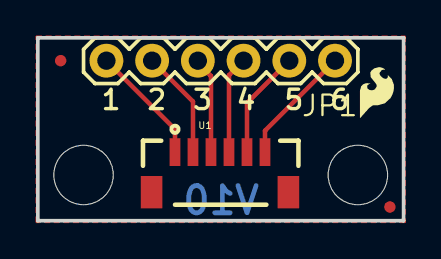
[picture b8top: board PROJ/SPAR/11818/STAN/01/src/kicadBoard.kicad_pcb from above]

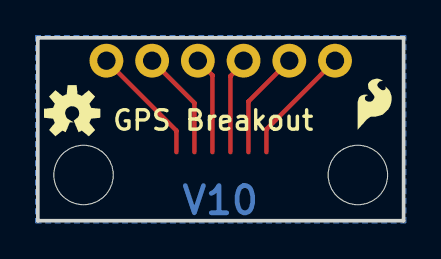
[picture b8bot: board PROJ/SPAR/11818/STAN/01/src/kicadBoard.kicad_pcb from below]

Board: 4 copper layers, 20.3 x 10.2 mm, 10 parts (2 on the bottom side), 6 nets.

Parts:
FID1, FID2: FIDUCIALUFIDUCIAL; MICRO-FIDUCIAL
FRAME2: FRAME-LETTER; CREATIVE_COMMONS
JP1: 1X06
JP2, JP7: LOGO-SFESK; SFE-LOGO-FLAME
JP4, JP6: STAND-OFF
LOGO1: OSHW-LOGOS; OSHW-LOGO-S
U1: JST_VERTICAL; JST-6-SMD-VERT-1.0MM

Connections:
GND: JP1.1, U1.6
unnamed: JP1.2, U1.5
unnamed: JP1.3, U1.4
unnamed: JP1.4, U1.3
unnamed: JP1.5, U1.2
unnamed: JP1.6, U1.1

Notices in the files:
parts and their libraries:
HTTP://CREATIVECOMMONS.ORG/LICENSES/BY-SA/3.0
RELEASED UNDER THE CREATIVE COMMONS ATTRIBUTION SHARE-ALIKE 3.0 LICENSE
HTTPS://CREATIVECOMMONS.ORG/LICENSES/BY-SA/4.0
RELEASED UNDER THE CREATIVE COMMONS ATTRIBUTION SHARE-ALIKE 4.0 LICENSE
